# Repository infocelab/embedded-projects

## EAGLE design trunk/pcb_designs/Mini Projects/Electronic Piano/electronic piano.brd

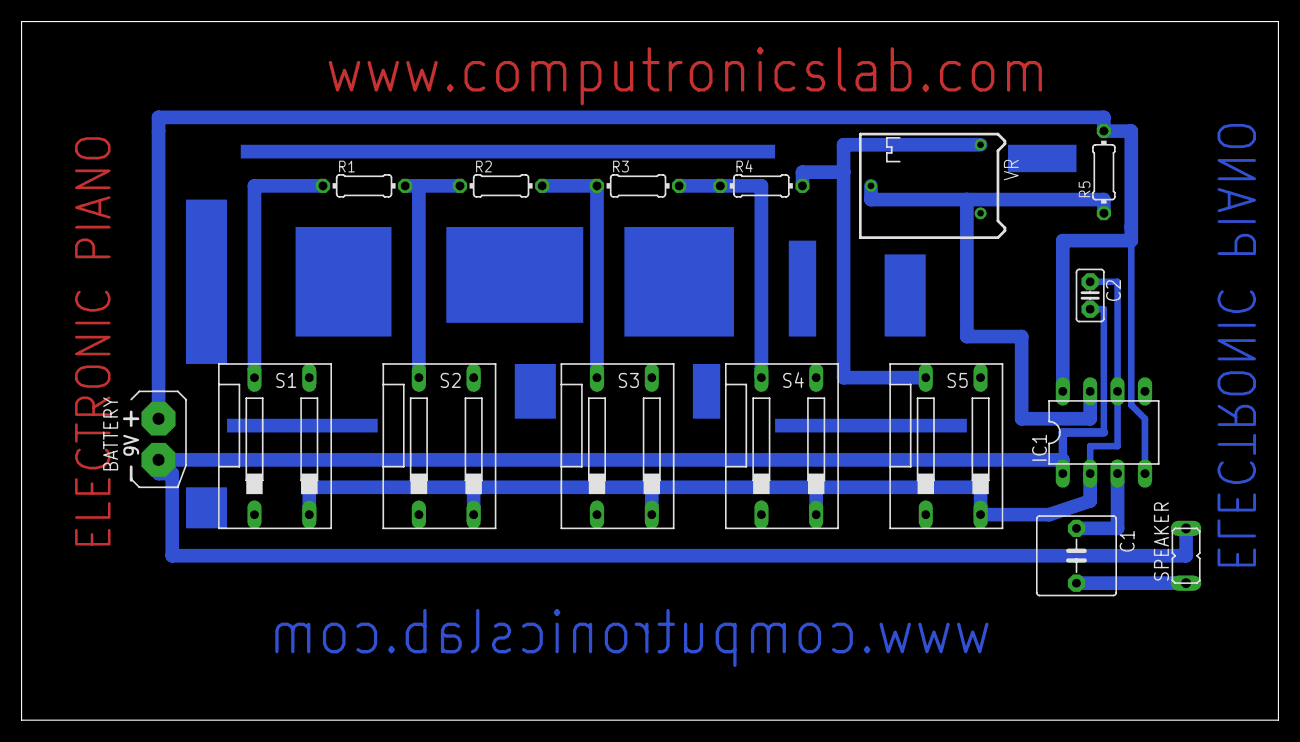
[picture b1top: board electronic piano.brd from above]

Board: 2 copper layers, 116.5 x 64.8 mm, 16 parts (0 on the bottom side), 11 nets.

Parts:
BATTERY: 9V; AB9V
C1: 10uf; C5B7.2
C2: 0.1uf; C2.5-2
IC1: NE555; DIL-08
R1, R2, R3, R4: 1k; 0204/7
R5: 4.7k; 0204/7
S1, S2, S3, S4, S5: PUSH SWITCH; DS-02
SPEAKER: 8 E; JP1
VR: 10k; RTRIM64P

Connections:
unnamed: R1.1, S1.4
unnamed: R1.2, R2.1, S2.4
unnamed: R3.2, R4.1, S4.4
unnamed: R4.2, S5.4, VR.1
unnamed: R2.2, R3.1, S3.4
unnamed: IC1.7, R5.1, VR.2
unnamed: C2.1, IC1.2, IC1.6, S1.2, S2.2, S3.2, S4.2, S5.2
unnamed: C1.1, IC1.3
unnamed: BATTERY.+, IC1.4, IC1.8, R5.2
unnamed: BATTERY.-, C2.2, IC1.1, SPEAKER.2
unnamed: C1.2, SPEAKER.1

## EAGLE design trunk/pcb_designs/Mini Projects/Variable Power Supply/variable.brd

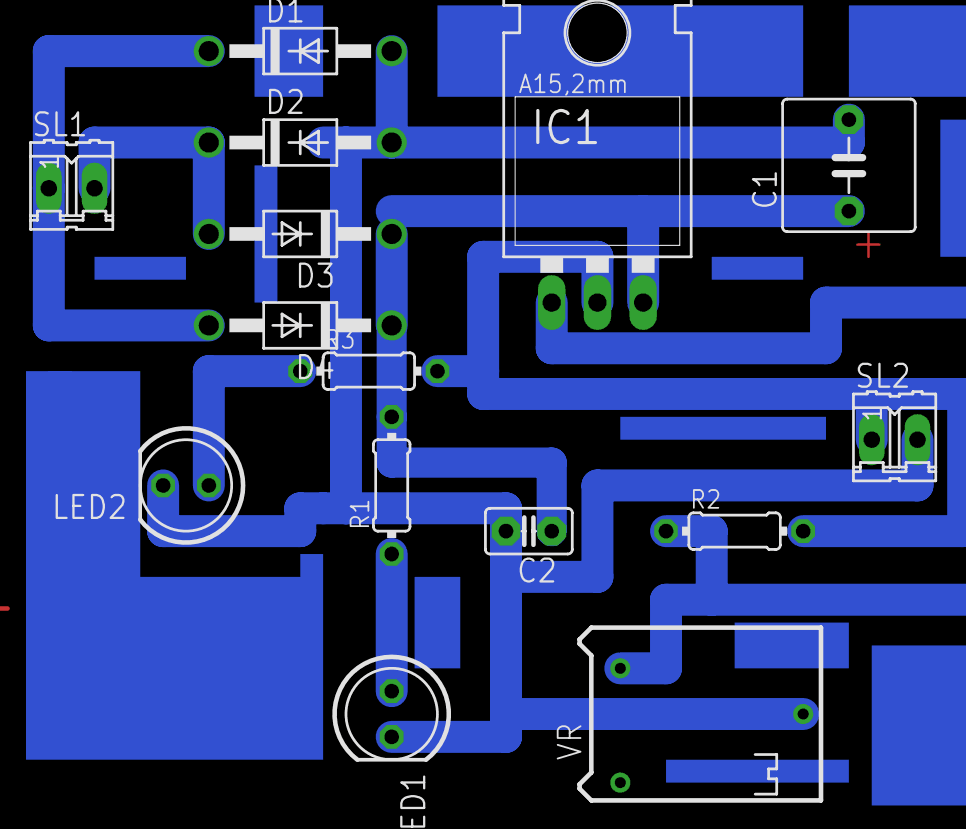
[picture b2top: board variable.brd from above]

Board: 2 copper layers, 15 parts (0 on the bottom side), 8 nets.

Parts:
C1: 2200uf; C5B7.2
C2: 0.1uf; C2.5-2
D1, D2, D3, D4: 1N4007; DO41-10
IC1: LM317; 317TL
LED1, LED2: 5mm; LED5MM
R1: 1K; 0204/7
R2: 180E; 0204/7
R3: 220E; 0204/7
SL1: transformer; 02P
SL2: output; 02P
VR: 4.7K; RTRIM64P

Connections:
unnamed: LED1.A, R1.1
unnamed: D1.C, D4.A, SL1.1
unnamed: D2.C, D3.A, SL1.2
unnamed: C1.1, C2.1, D3.C, D4.C, IC1.3, R1.2
unnamed: IC1.1, R2.1, VR.3
unnamed: LED2.A, R3.1
unnamed: IC1.2, R2.2, R3.2, SL2.1
unnamed: C1.2, C2.2, D1.A, D2.A, LED1.K, LED2.K, SL2.2, VR.2

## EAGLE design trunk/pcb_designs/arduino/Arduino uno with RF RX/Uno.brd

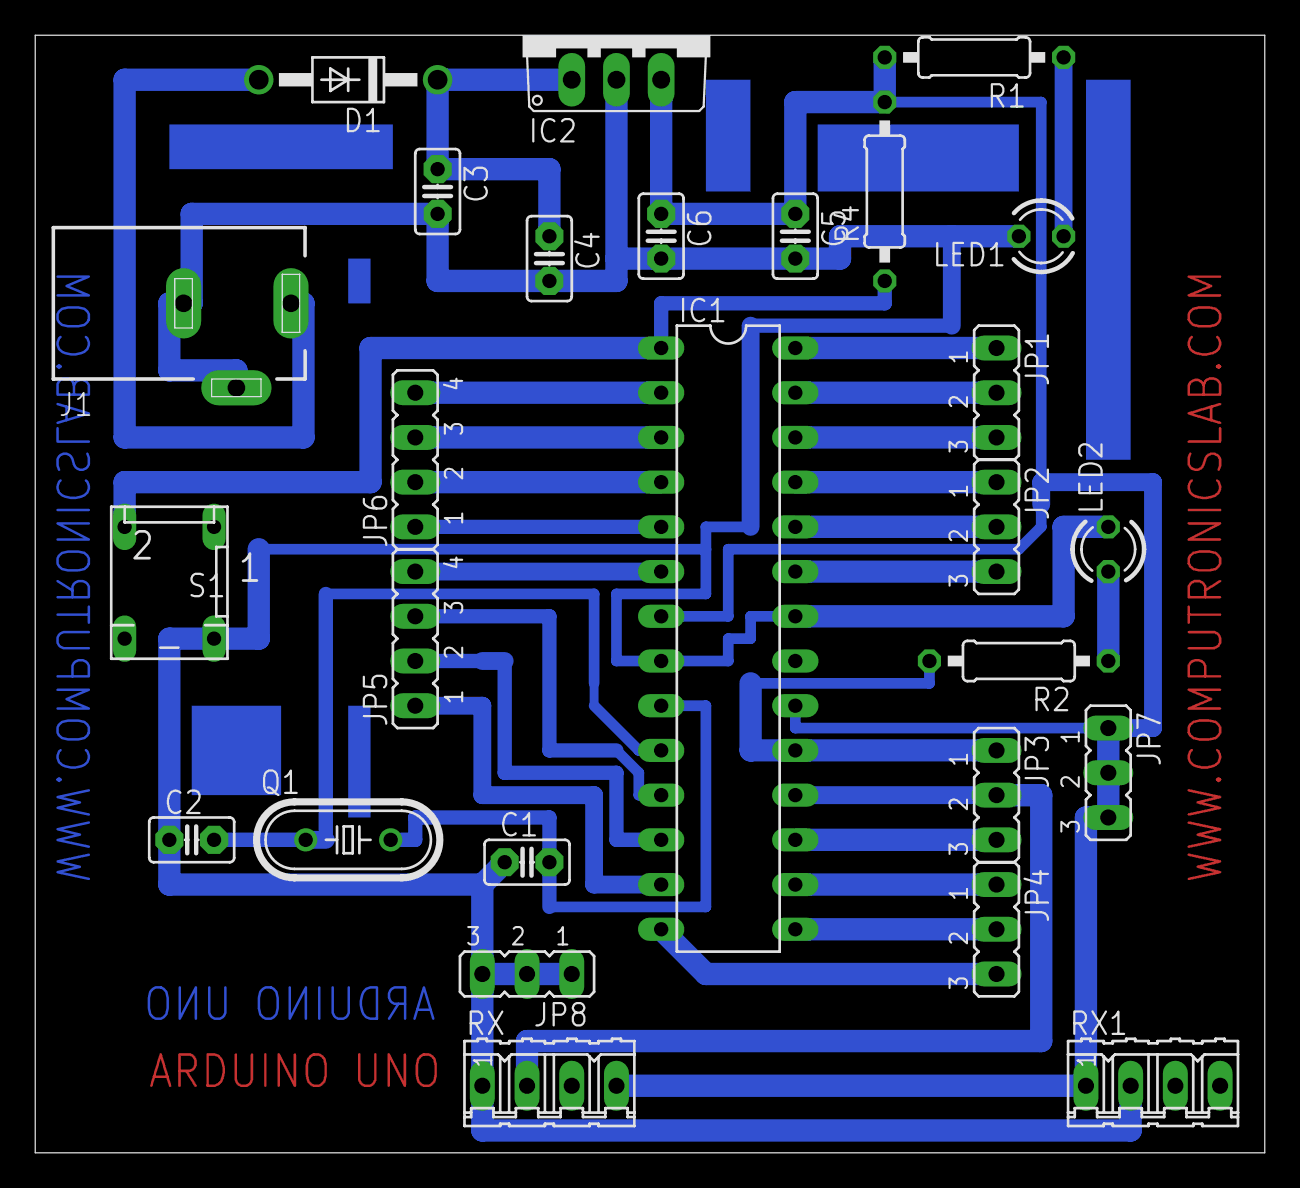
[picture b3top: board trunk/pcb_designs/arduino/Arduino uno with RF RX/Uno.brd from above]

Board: 2 copper layers, 69.8 x 63.5 mm, 27 parts (0 on the bottom side), 29 nets.

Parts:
C1, C2: 22pf; C2.5-2
C3: 470uF; C2.5-2
C4, C5: 0.1uf; C2.5-2
C6: 4.7uf; C2.5-2
D1: 1N4007; DO41-10
IC1: ATMEGA328; DIL28-3
IC2: 7805; TO220V
J1: DCJ0303
JP1, JP2, JP3, JP4: 3 pin; JP2
JP5, JP6: 4 pin; JP4
JP7, JP8: JP2
LED1, LED2: 3mm; LED3MM
Q1: 16MHZ; HC49/S
R1: 220R; 0207/10
R2: 330R; 0207/10
R4: 10K; 0207/10
RX, RX1: 04P
S1: push switch; DP-02

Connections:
unnamed: C1.2, IC1.9, Q1.2
unnamed: C2.2, IC1.10, Q1.1
unnamed: D1.A, J1.1
unnamed: C5.1, C6.1, IC1.7, IC1.20, IC2.3, JP7.1, JP7.2, JP7.3, R1.2, R4.2, RX.4, RX1.1
unnamed: C1.1, C2.1, C3.2, C4.2, C5.2, C6.2, IC1.8, IC1.22, IC2.2, J1.2, J1.3, JP8.1, JP8.2, JP8.3, LED1.K, LED2.K, RX.1, RX1.2, S1.4
unnamed: LED1.A, R1.1
unnamed: C3.1, C4.1, D1.C, IC2.1
unnamed: IC1.28, JP1.1
unnamed: IC1.27, JP1.2
unnamed: IC1.26, JP1.3
unnamed: IC1.25, JP2.1
unnamed: IC1.24, JP2.2
unnamed: IC1.23, JP2.3
unnamed: IC1.5, JP6.1
unnamed: IC1.2, JP6.4
unnamed: IC1.3, JP6.3
unnamed: IC1.4, JP6.2
unnamed: IC1.6, JP5.4
unnamed: IC1.12, JP5.2
unnamed: IC1.11, JP5.3
unnamed: IC1.17, JP3.3
unnamed: IC1.14, JP4.3
unnamed: IC1.15, JP4.2
unnamed: IC1.16, JP4.1
unnamed: IC1.18, JP3.2, RX.2
unnamed: IC1.19, JP3.1, R2.2
unnamed: IC1.13, JP5.1
unnamed: IC1.1, R4.1, S1.2
unnamed: LED2.A, R2.1

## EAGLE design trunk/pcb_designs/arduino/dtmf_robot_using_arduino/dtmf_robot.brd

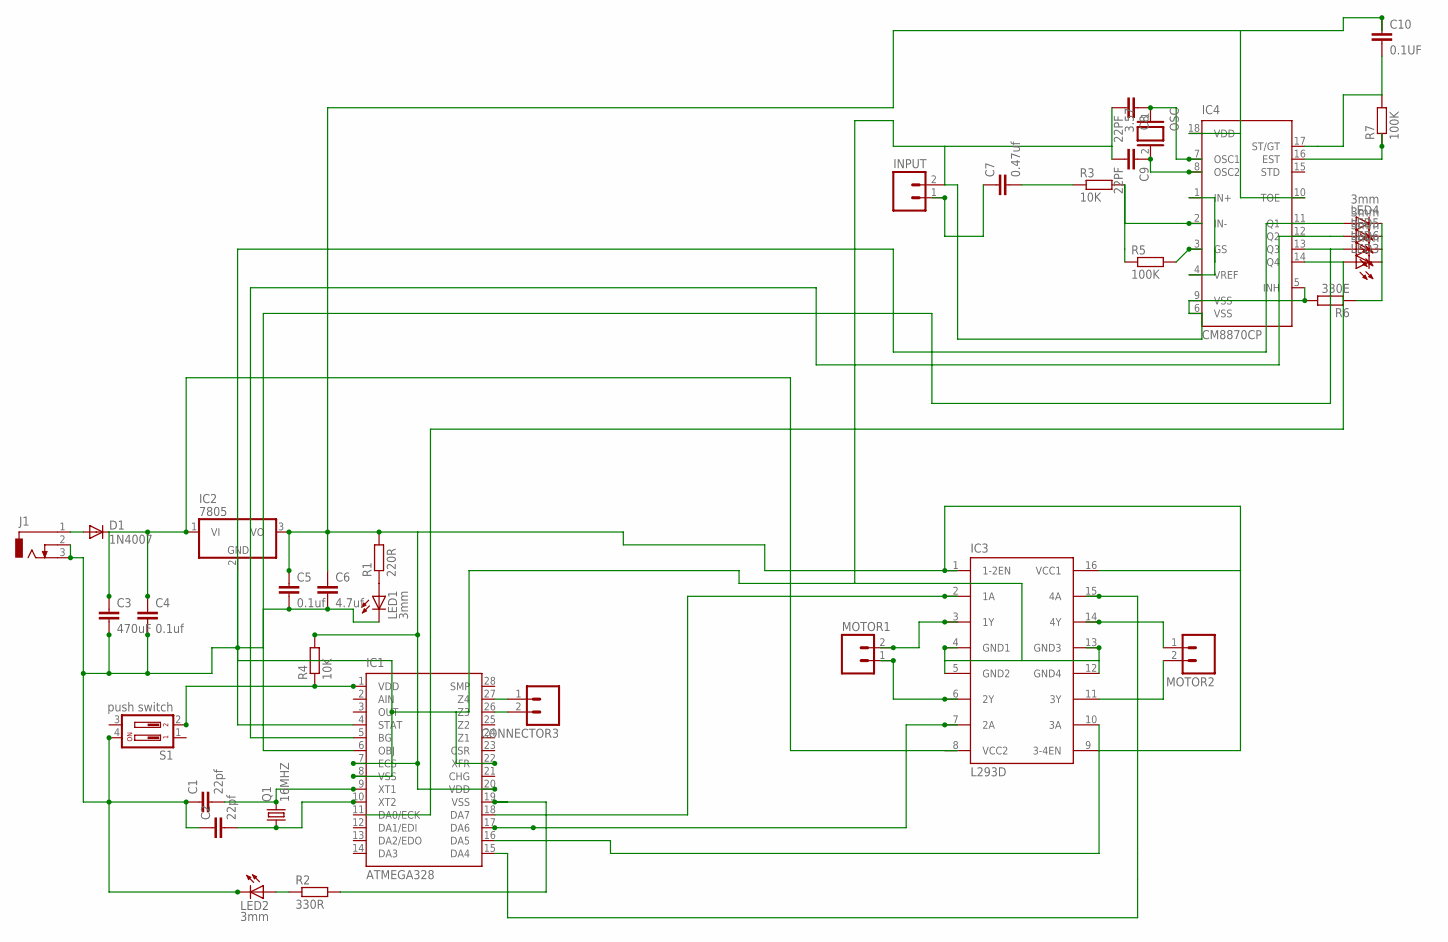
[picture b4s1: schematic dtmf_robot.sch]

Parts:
C1, C2: 22pf; C2.5-2
C3: 470uF; C2.5-2
C4, C5: 0.1uf; C2.5-2
C6: 4.7uf; C2.5-2
C7: 0.47uf; C2.5-2
C8, C9: 22PF; C2.5-2
C10: 0.1UF; C2.5-2
CONNECTOR3: M02; 02P
D1: 1N4007; DO41-10
IC1: ATMEGA328; DIL28-3
IC2: 7805; TO220V
IC3: L293D; DIL16
IC4: CM8870CP; DIL18
INPUT: M02; 02P
J1: DCJ0303
LED1, LED2, LED3, LED4, LED5, LED6: 3mm; LED3MM
MOTOR1, MOTOR2: M02; 02P
OSC: 3.57; QS
Q1: 16MHZ; HC49/S
R1: 220R; 0207/10
R2: 330R; 0207/10
R3: 10K; 0204/7
R4: 10K; 0207/10
R5, R7: 100K; 0204/7
R6: 330E; 0204/7
S1: push switch; DP-02

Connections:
unnamed: C1.2, IC1.9 (XT1), Q1.2
unnamed: C2.2, IC1.10 (XT2), Q1.1
unnamed: D1.A, J1.1
unnamed: C3.1, C4.1, D1.C, IC2.1 (VI), IC3.8 (VCC2)
unnamed: C1.1, C2.1, C3.2, C4.2, C5.2, C6.2, C8.2, C9.2, IC1.8 (VSS), IC1.22 (XFR), IC2.2 (GND), IC3.4 (GND1), IC3.5 (GND2), IC3.12 (GND4), IC3.13 (GND3), IC4.5 (INH), IC4.6 (VSS), IC4.9 (VSS), INPUT.2, J1.2, J1.3, LED1.K (C), LED2.K (C), R6.2, S1.4
unnamed: LED1.A, R1.1
unnamed: IC1.17 (DA6), IC3.7 (2A)
unnamed: IC1.4 (STAT), IC4.11 (Q1), LED4.A
unnamed: IC1.5 (BG), IC4.12 (Q2), LED5.A
unnamed: IC1.6 (OBJ), IC4.13 (Q3), LED6.A
unnamed: IC4.14 (Q4), LED3.A
unnamed: CONNECTOR3.1, IC1.27 (Z4)
unnamed: CONNECTOR3.2, IC1.26 (Z3)
unnamed: IC1.18 (DA7), IC3.2 (1A)
unnamed: IC1.15 (DA4), IC3.15 (4A)
unnamed: C7.2, R3.1
unnamed: IC1.16 (DA5), IC3.10 (3A)
unnamed: C10.2, IC4.17 (ST/GT), R7.2
unnamed: IC3.14 (4Y), MOTOR2.1
unnamed: IC1.19 (VSS), R2.2
unnamed: IC3.11 (3Y), MOTOR2.2
unnamed: IC1.1 (VDD), R4.1, S1.2
unnamed: LED2.A, R2.1
unnamed: IC3.6 (2Y), MOTOR1.1
unnamed: IC3.3 (1Y), MOTOR1.2
unnamed: LED3.K (C), LED4.K (C), LED5.K (C), LED6.K (C), R6.1
unnamed: C5.1, C6.1, C10.1, IC1.7 (ECS), IC1.20 (VDD), IC2.3 (VO), IC3.1 (1-2EN), IC3.9 (3-4EN), IC3.16 (VCC1), IC4.10 (TOE), IC4.18 (VDD), R1.2, R4.2
unnamed: C7.1, INPUT.1
unnamed: IC4.2 (IN-), R3.2, R5.1
unnamed: IC4.1 (IN+), IC4.4 (VREF)
unnamed: IC4.3 (GS), R5.2
unnamed: C8.1, IC4.7 (OSC1), OSC.1
unnamed: C9.1, IC4.8 (OSC2), OSC.2
unnamed: IC4.16 (EST), R7.1

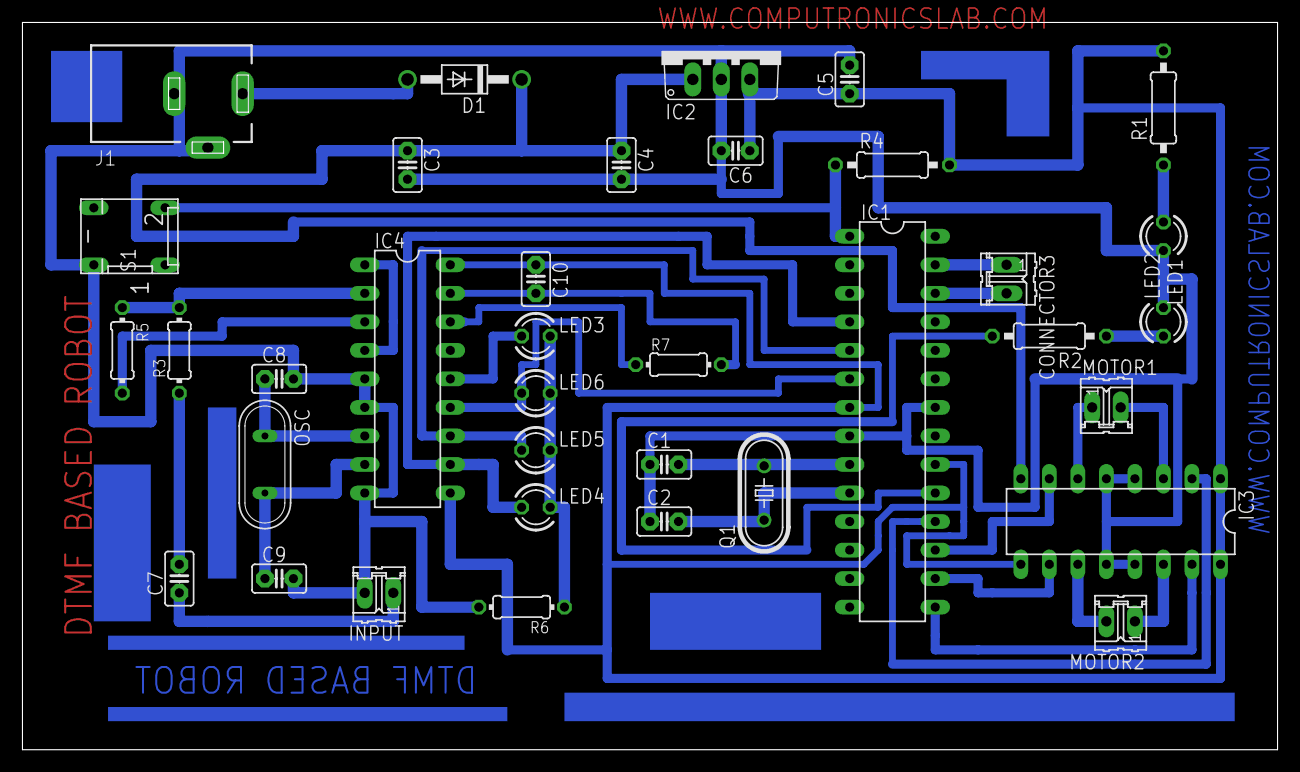
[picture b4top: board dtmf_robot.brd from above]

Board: 2 copper layers, 111.8 x 64.8 mm, 36 parts (0 on the bottom side), 34 nets.

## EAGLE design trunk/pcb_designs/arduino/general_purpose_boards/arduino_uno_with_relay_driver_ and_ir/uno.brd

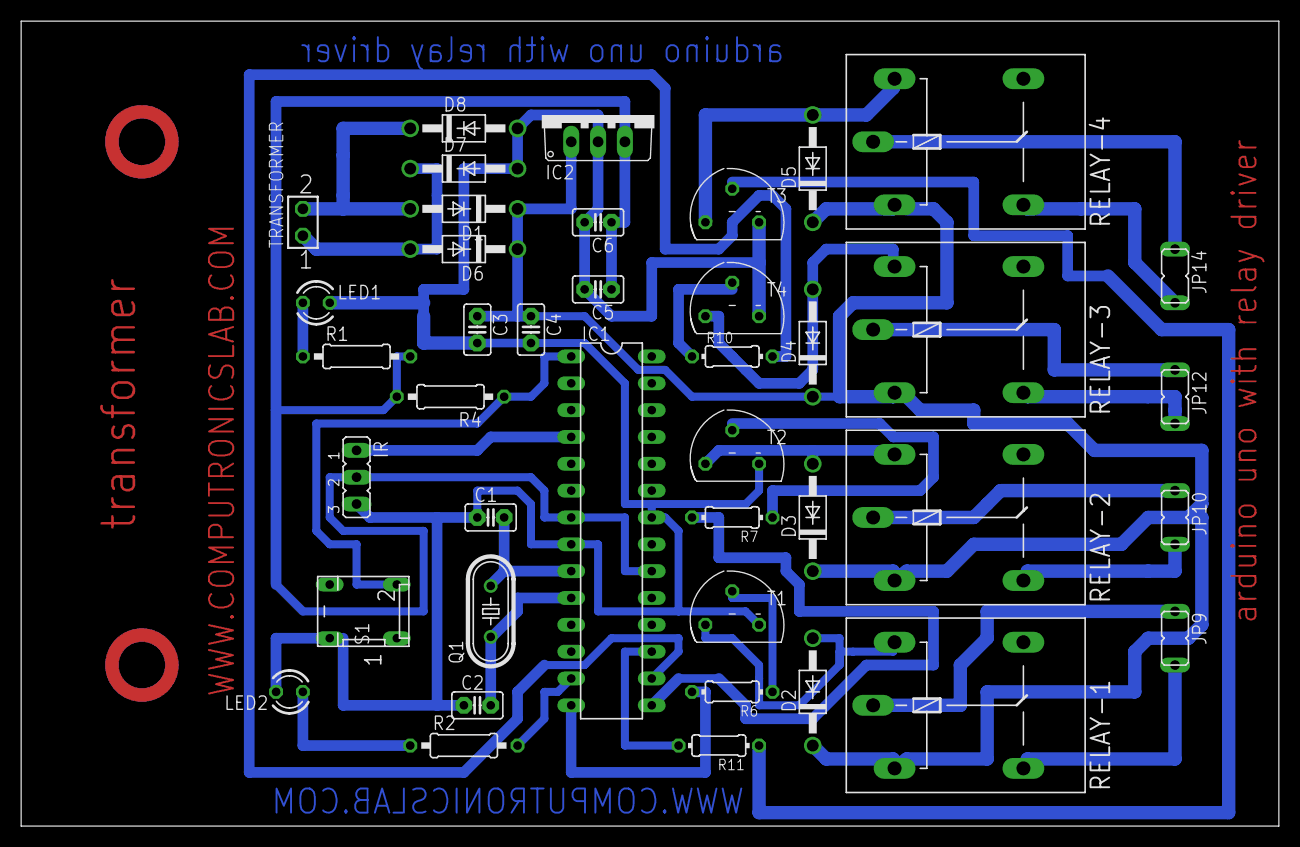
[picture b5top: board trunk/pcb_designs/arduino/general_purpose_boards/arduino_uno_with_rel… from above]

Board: 2 copper layers, 119.0 x 76.2 mm, 41 parts (0 on the bottom side), 32 nets.

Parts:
C1, C2: 22pf; C2.5-2
C3: 470uF; C2.5-2
C4, C5: 0.1uf; C2.5-2
C6: 4.7uf; C2.5-2
D1, D2, D3, D4, D5, D6, D7, D8: 1N4007; DO41-10
IC1: ATMEGA328; DIL28-3
IC2: 7805; TO220V
IR: 3 pin; JP2
JP9, JP10, JP12, JP14: AC CONNECTOR; JP1
LED1, LED2: LED3MM
Q1: 16MHZ; HC49/S
R1: 220R; 0207/10
R2: 330R; 0207/10
R4: 10K; 0207/10
R6, R7, R10, R11: 5.6K; 0204/7
RELAY-1, RELAY-2, RELAY-3, RELAY-4: 12V; G5LE
S1: DP-02
T1, T2, T3, T4: BC547; TO92
TRANSFORMER: hole; SSW-101-02-S-D

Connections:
unnamed: C1.2, IC1.9, Q1.2
unnamed: C2.2, IC1.10, Q1.1
unnamed: D6.A, D7.C, TRANSFORMER.1
unnamed: C5.1, C6.1, IC1.7, IC1.20, IC2.3, IR.2, R1.2, R4.2
unnamed: LED1.A, R1.1
unnamed: C3.1, C4.1, D1.C, D2.C, D3.C, D4.C, D5.C, D6.C, IC2.1, RELAY-1.1, RELAY-2.1, RELAY-3.1, RELAY-4.1
unnamed: IC1.4, IR.1
unnamed: D1.A, D8.C, TRANSFORMER.2
unnamed: IC1.13, R2.2
unnamed: C1.1, C2.1, C3.2, C4.2, C5.2, C6.2, D7.A, D8.A, IC1.8, IC1.22, IC2.2, IR.3, LED1.K, LED2.K, S1.4, T1.1, T2.1, T3.1, T4.1
unnamed: D2.A, RELAY-1.2, T1.3
unnamed: R7.1, T2.2
unnamed: R6.1, T1.2
unnamed: IC1.1, R4.1, S1.2
unnamed: LED2.A, R2.1
unnamed: JP9.2, RELAY-1.S
unnamed: JP9.1, RELAY-1.P
unnamed: JP10.2, RELAY-2.S
unnamed: JP10.1, RELAY-2.P
unnamed: IC1.14, R6.2
unnamed: D3.A, RELAY-2.2, T2.3
unnamed: D4.A, RELAY-3.2, T4.3
unnamed: R11.1, T3.2
unnamed: R10.1, T4.2
unnamed: JP12.2, RELAY-3.S
unnamed: JP12.1, RELAY-3.P
unnamed: JP14.2, RELAY-4.S
unnamed: JP14.1, RELAY-4.P
unnamed: IC1.16, R10.2
unnamed: IC1.17, R11.2
unnamed: D5.A, RELAY-4.2, T3.3
unnamed: IC1.15, R7.2
